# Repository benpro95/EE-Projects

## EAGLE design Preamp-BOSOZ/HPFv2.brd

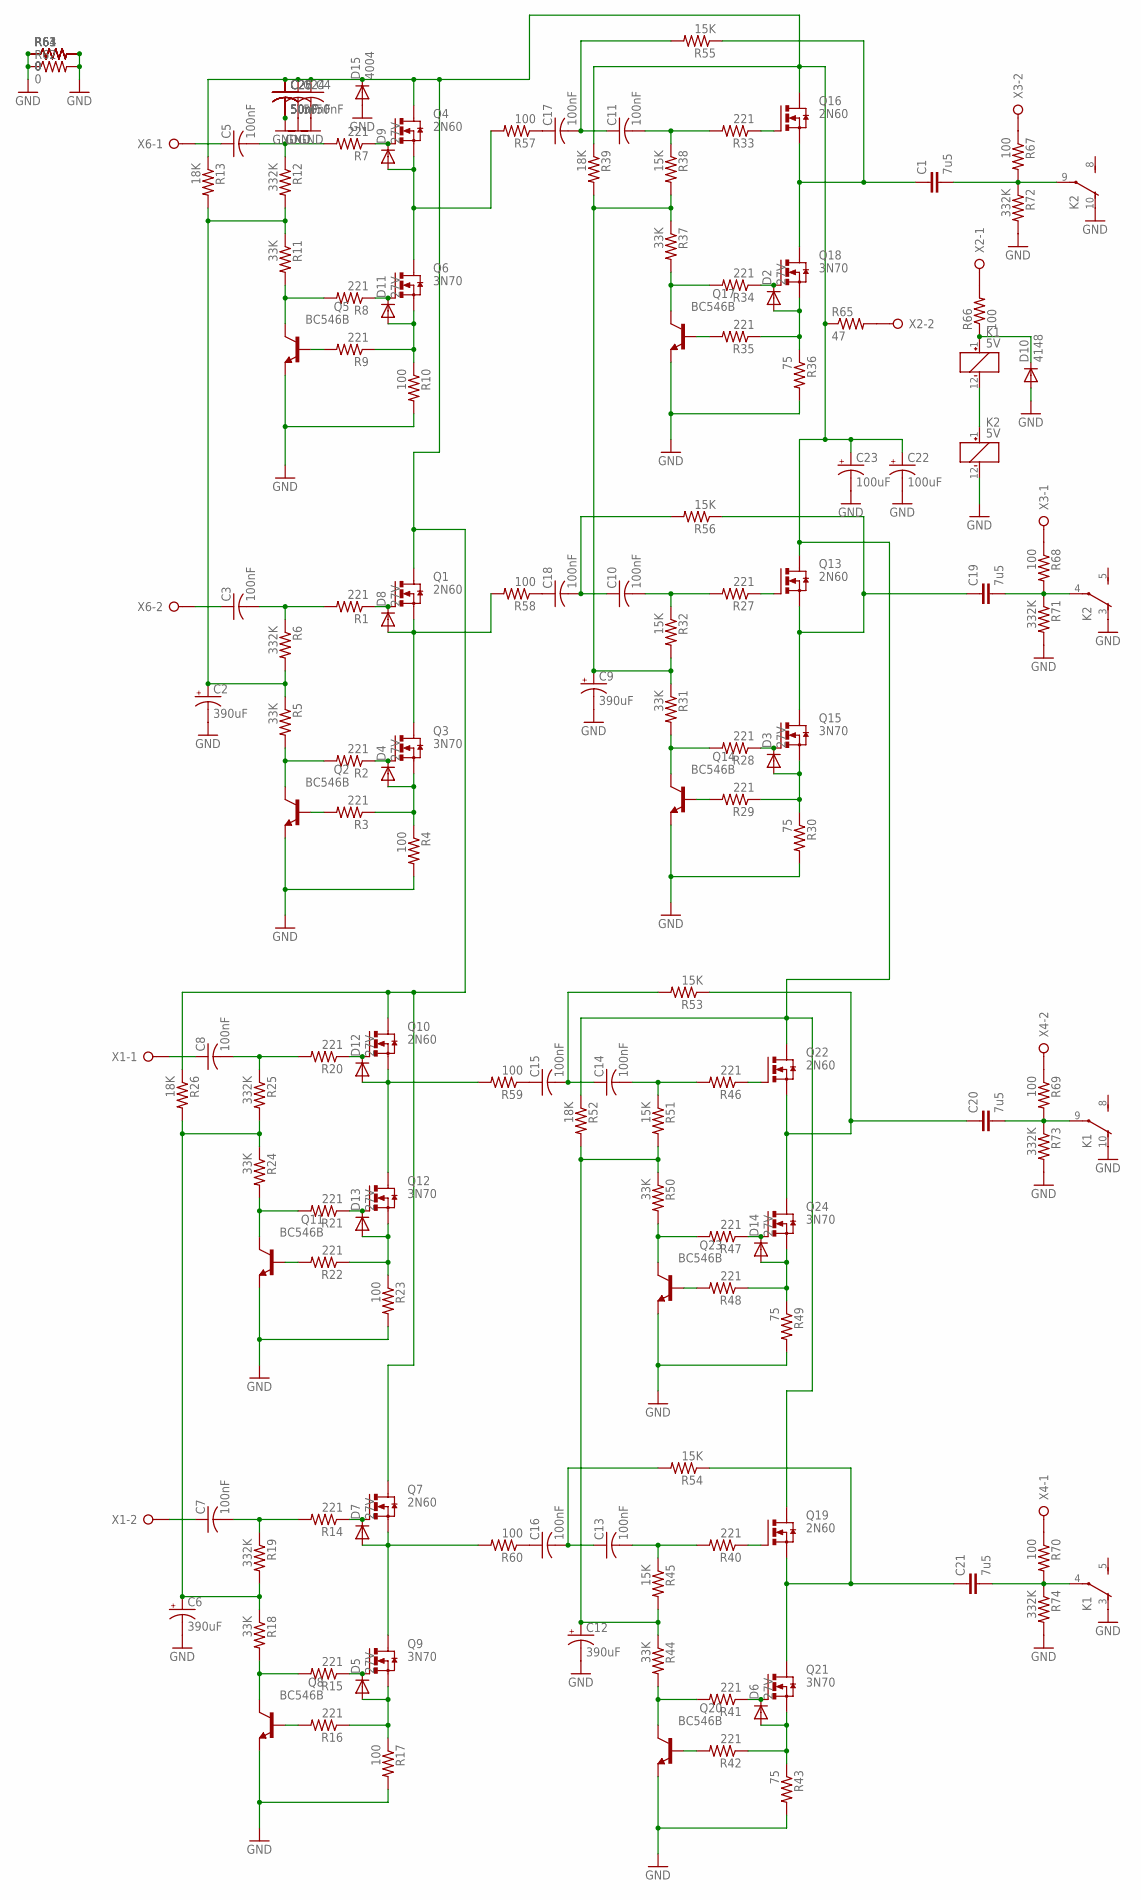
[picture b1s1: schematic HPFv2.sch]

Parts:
C1, C19, C20, C21: 7u5; C37.5B20
C2, C6, C9, C12: 390uF; E5-13
C3, C5, C7, C8, C10, C11, C13, C14, C15, C16, C17, C18: 100nF; C050-075X075
C4, C24, C25, C26, C27: 50nF; C075-042X103
C22, C23: 100uF; E5-13
D2, D3, D4, D5, D6, D7, D8, D9, D11, D12, D13, D14: 27V; DO35-7
D10: 4148; DO35-7
D15: 4004; DO35-10
K1, K2: 5V; TX2
Q1, Q4, Q7, Q10, Q13, Q16, Q19, Q22: 2N60; TO220BH
Q2, Q5, Q8, Q11, Q14, Q17, Q20, Q23: BC546B; TO92-EBC
Q3, Q6, Q9, Q12, Q15, Q18, Q21, Q24: 3N70; TO220BH
R1, R2, R3, R7, R8, R9, R14, R15, R16, R20, R21, R22, R27, R28, R29, R33, R34, R35, R40, R41, R42, R46, R47, R48: 221; 0207/10
R4, R10, R17, R23, R57, R58, R59, R60, R67, R68, R69, R70: 100; 0207/10
R5, R11, R18, R24, R31, R37, R44, R50: 33K; 0207/10
R6, R12, R19, R25, R71, R72, R73, R74: 332K; 0207/10
R13, R26, R39, R52: 18K; 0207/10
R30, R36, R43, R49: 75; 0207/10
R32, R38, R45, R51, R53, R54, R55, R56: 15K; 0207/10
R61, R63, R64: 0; 0207/10
R62: 0; 0204/7
R65: 47; 0617/22
R66: 100; 0309/12
X1, X2, X3, X4, X6: W237-02P; W237-132

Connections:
GND: C2.-, C4.2, C6.-, C9.-, C12.-, C22.-, C23.-, C24.2, C25.2, C26.2, C27.2, D10.A, D15.A, K1.3 (O), K1.10 (O), K2.3 (O), K2.10 (O), K2.12 (-), Q2.E, Q5.E, Q8.E, Q11.E, Q14.E, Q17.E, Q20.E, Q23.E, R4.2, R10.2, R17.2, R23.2, R30.2, R36.2, R43.2, R49.2, R61.1, R61.2, R62.1, R62.2, R63.1, R63.2, R64.1, R64.2, R71.2, R72.2, R73.2, R74.2
unnamed: Q2.B, R3.2
unnamed: D4.A, Q3.S, R3.1, R4.1
unnamed: D4.C, Q3.G, R2.1
unnamed: Q2.C, R2.2, R5.2
unnamed: C3.2, R1.2, R6.1
unnamed: D8.A, Q1.S, Q3.D, R58.2
unnamed: D8.C, Q1.G, R1.1
unnamed: C5.1, X6.1
unnamed: Q5.B, R9.2
unnamed: D11.A, Q6.S, R9.1, R10.1
unnamed: D11.C, Q6.G, R8.1
unnamed: Q5.C, R8.2, R11.2
unnamed: D9.A, Q4.S, Q6.D, R57.2
unnamed: D9.C, Q4.G, R7.1
unnamed: C5.2, R7.2, R12.1
unnamed: C2.+, R5.1, R6.2, R11.1, R12.2, R13.2
unnamed: C4.1, C22.+, C23.+, C24.1, C25.1, C26.1, C27.1, D15.C, Q1.D, Q4.D, Q7.D, Q10.D, Q13.D, Q16.D, Q19.D, Q22.D, R13.1, R26.1, R39.1, R52.1, R65.1
unnamed: C3.1, X6.2
unnamed: Q8.B, R16.2
unnamed: D5.A, Q9.S, R16.1, R17.1
unnamed: D5.C, Q9.G, R15.1
unnamed: Q8.C, R15.2, R18.2
unnamed: D7.A, Q7.S, Q9.D, R60.2
unnamed: D7.C, Q7.G, R14.1
unnamed: C7.2, R14.2, R19.1
unnamed: Q11.B, R22.2
unnamed: D13.A, Q12.S, R22.1, R23.1
unnamed: D13.C, Q12.G, R21.1
unnamed: Q11.C, R21.2, R24.2
unnamed: D12.A, Q10.S, Q12.D, R59.2
unnamed: D12.C, Q10.G, R20.1
unnamed: C8.2, R20.2, R25.1
unnamed: C6.+, R18.1, R19.2, R24.1, R25.2, R26.2
unnamed: C21.2, K1.4, R70.2, R74.1
unnamed: C8.1, X1.1
unnamed: C7.1, X1.2
unnamed: Q14.B, R29.2
unnamed: D3.A, Q15.S, R29.1, R30.1
unnamed: D3.C, Q15.G, R28.1
unnamed: Q14.C, R28.2, R31.2
unnamed: C19.1, Q13.S, Q15.D, R56.1
unnamed: Q13.G, R27.1
unnamed: C10.2, R27.2, R32.1
unnamed: Q17.B, R35.2
unnamed: D2.A, Q18.S, R35.1, R36.1
unnamed: D2.C, Q18.G, R34.1
unnamed: Q17.C, R34.2, R37.2
unnamed: C1.1, Q16.S, Q18.D, R55.1
unnamed: Q16.G, R33.1
unnamed: C11.2, R33.2, R38.1
unnamed: C9.+, R31.1, R32.2, R37.1, R38.2, R39.2
unnamed: C20.2, K1.9, R69.2, R73.1
unnamed: C11.1, C17.2, R55.2
unnamed: C10.1, C18.2, R56.2
unnamed: Q20.B, R42.2
unnamed: D6.A, Q21.S, R42.1, R43.1
unnamed: D6.C, Q21.G, R41.1
unnamed: Q20.C, R41.2, R44.2
unnamed: C21.1, Q19.S, Q21.D, R54.1
unnamed: Q19.G, R40.1
unnamed: C13.2, R40.2, R45.1
unnamed: Q23.B, R48.2
unnamed: D14.A, Q24.S, R48.1, R49.1
unnamed: D14.C, Q24.G, R47.1
unnamed: Q23.C, R47.2, R50.2
unnamed: C20.1, Q22.S, Q24.D, R53.1
unnamed: Q22.G, R46.1
unnamed: C14.2, R46.2, R51.1
unnamed: C12.+, R44.1, R45.2, R50.1, R51.2, R52.2
unnamed: C19.2, K2.4, R68.2, R71.1
unnamed: C14.1, C15.2, R53.2
unnamed: C13.1, C16.2, R54.2
unnamed: C17.1, R57.1
unnamed: C18.1, R58.1
unnamed: C15.1, R59.1
unnamed: C16.1, R60.1
unnamed: C1.2, K2.9, R67.2, R72.1
unnamed: R65.2, X2.2
unnamed: D10.C, K1.1 (+), R66.1
unnamed: R66.2, X2.1
unnamed: R68.1, X3.1
unnamed: R67.1, X3.2
unnamed: R69.1, X4.2
unnamed: R70.1, X4.1
unnamed: K1.12 (-), K2.1 (+)

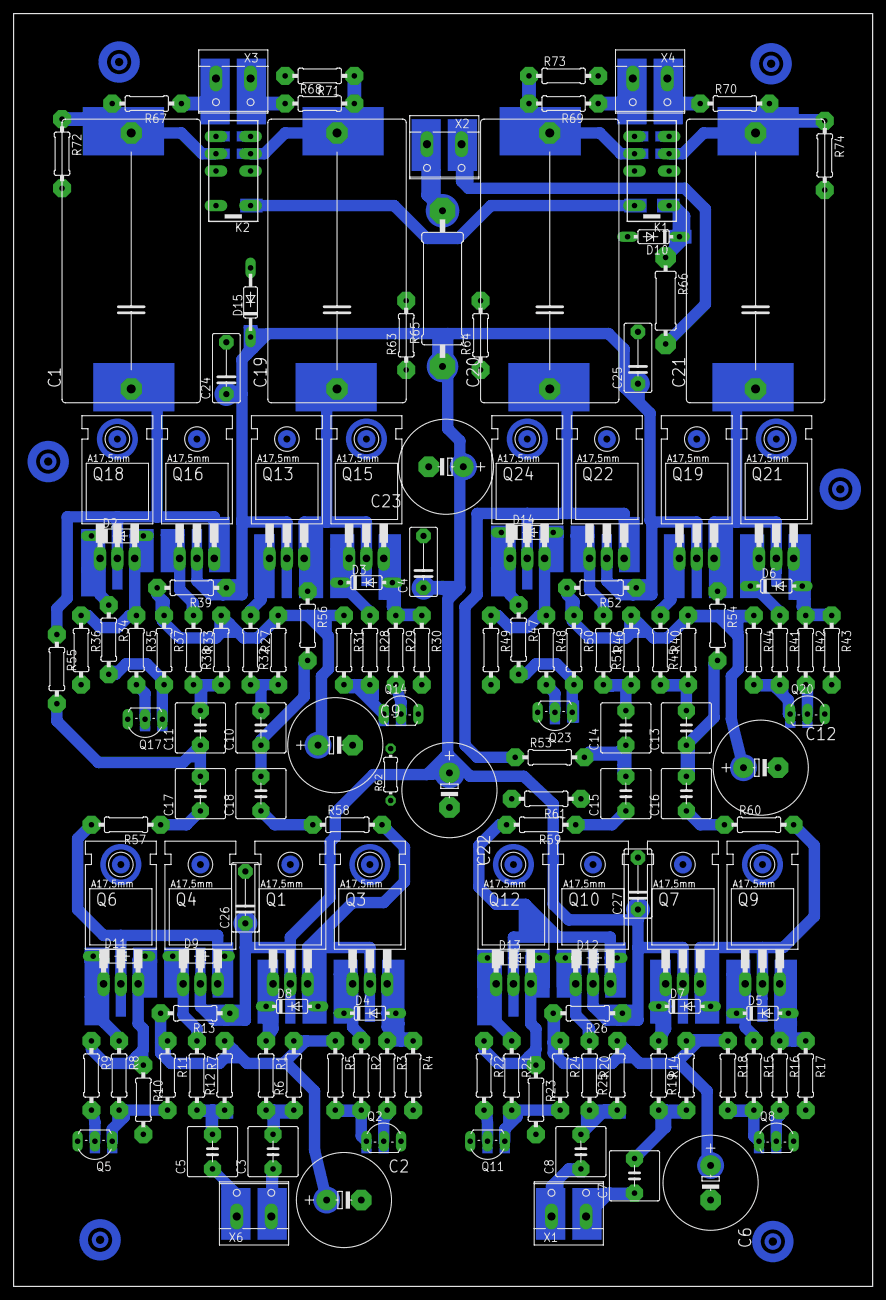
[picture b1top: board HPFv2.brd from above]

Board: 2 copper layers, 126.2 x 186.9 mm, 146 parts (0 on the bottom side), 86 nets.

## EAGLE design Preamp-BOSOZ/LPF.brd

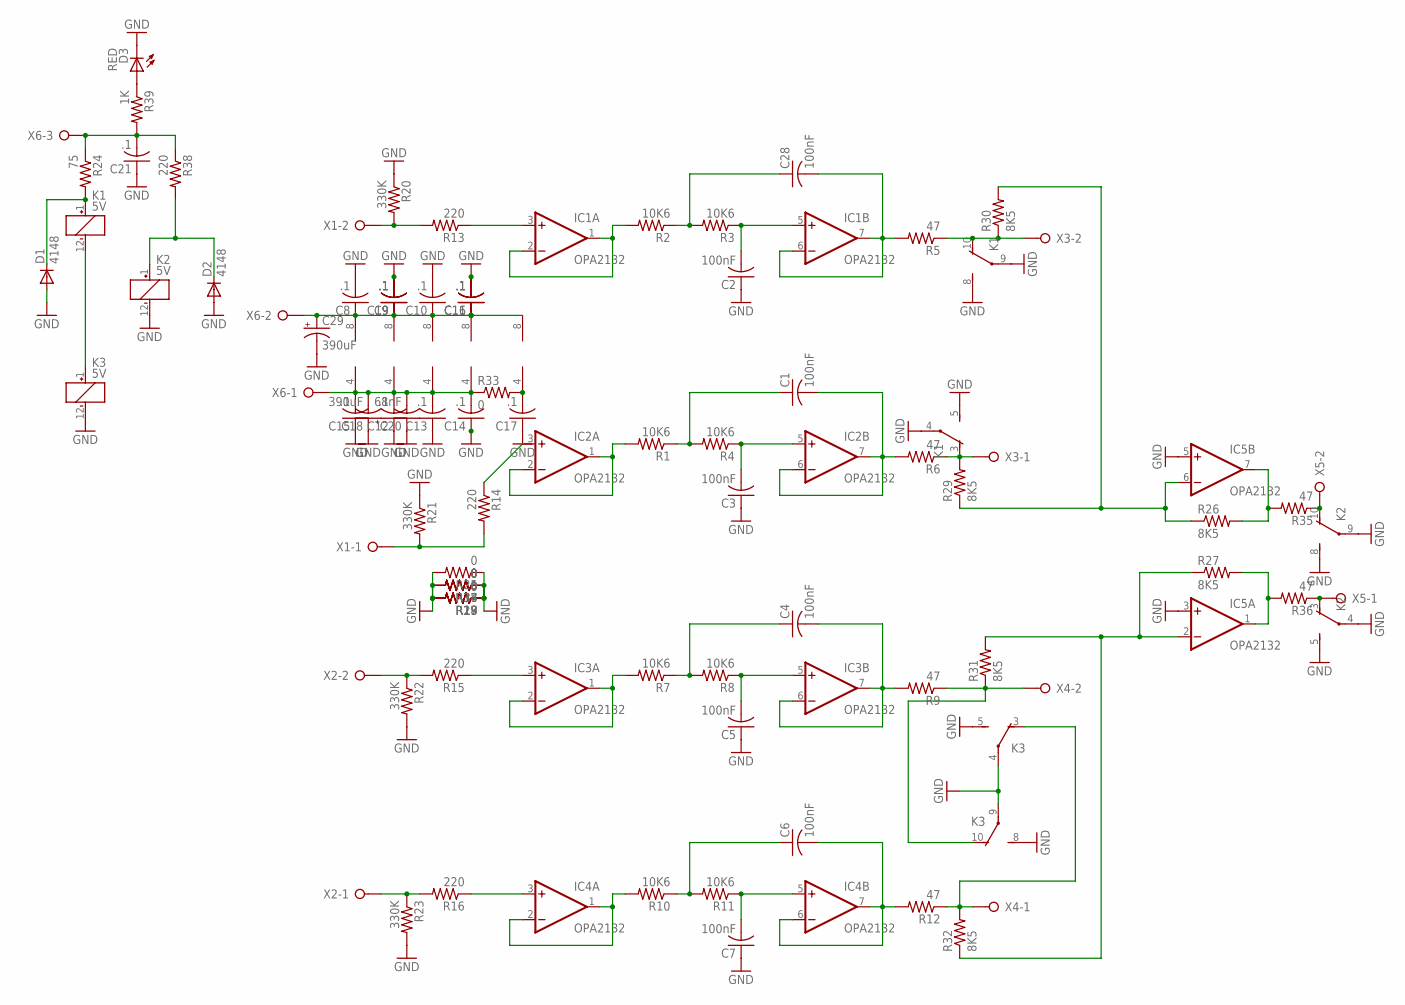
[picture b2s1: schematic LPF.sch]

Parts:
C1, C2, C3, C4, C5, C6, C7, C28: 100nF; C050-075X075
C8, C9, C10, C11, C12, C13, C14, C15, C16, C17, C19, C21: .1; C4532
C18, C29: 390uF; E5-13
C20: 68nF; C075-042X103
D1, D2: 4148; DO35-7
D3: RED; SFH482
IC1, IC2, IC3, IC4, IC5: OPA2132; DIL08
K1, K2, K3: 5V; TX2; MPN TX2-12V
R1, R2, R3, R4, R7, R8, R10, R11: 10K6; 0207/10
R5, R6, R9: 47; 0207/12
R12, R35, R36: 47; 0207/10
R13, R14, R15, R16: 220; 0207/10
R17, R18, R19, R25, R28, R34: 0; 0204/7
R20, R21, R22, R23: 330K; R1210
R24: 75; 0207/10
R26, R27, R29, R30, R31, R32: 8K5; R1210
R33: 0; 0207/12
R37: 0; 0207/10
R38: 220; 0309/12
R39: 1K; 0207/10
X1, X2, X3, X4, X5: W237-02P; W237-132
X6: W237-3E

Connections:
GND: C2.1, C3.1, C5.1, C7.1, C8.2, C9.2, C10.2, C11.2, C12.1, C13.1, C14.1, C15.1, C16.2, C17.1, C18.+, C19.2, C20.1, C21.1, C29.-, D1.A, D2.A, D3.K (C), IC5.3 (+IN), IC5.5 (+IN), K1.4, K1.5 (S), K1.8 (S), K1.9, K2.4, K2.5 (S), K2.8 (S), K2.9, K2.12 (-), K3.4, K3.5 (S), K3.8 (S), K3.9, K3.12 (-), R17.1, R17.2, R18.1, R18.2, R19.1, R19.2, R20.1, R21.1, R22.2, R23.2, R25.1, R25.2, R28.1, R28.2, R34.1, R34.2, R37.1, R37.2
unnamed: IC1.1 (OUT), IC1.2 (-IN), R2.2
unnamed: C28.2, IC1.6 (-IN), IC1.7 (OUT), R5.2
unnamed: C2.2, IC1.5 (+IN), R3.1
unnamed: C28.1, R2.1, R3.2
unnamed: IC1.3 (+IN), R13.1
unnamed: R14.2, R21.2, X1.1
unnamed: R13.2, R20.2, X1.2
unnamed: IC2.1 (OUT), IC2.2 (-IN), R1.2
unnamed: IC2.3 (+IN), R14.1
unnamed: C1.2, IC2.6 (-IN), IC2.7 (OUT), R6.2
unnamed: C3.2, IC2.5 (+IN), R4.1
unnamed: C1.1, R1.1, R4.2
unnamed: C12.2, C13.2, C14.2, C15.2, C18.-, C20.2, IC1.4 (V-), IC2.4 (V-), IC3.4 (V-), IC4.4 (V-), R33.1, X6.1
unnamed: C8.1, C9.1, C10.1, C11.1, C16.1, C19.1, C29.+, IC1.8 (V+), IC2.8 (V+), IC3.8 (V+), IC4.8 (V+), IC5.8 (V+), X6.2
unnamed: IC3.1 (OUT), IC3.2 (-IN), R7.2
unnamed: IC3.3 (+IN), R15.1
unnamed: C4.2, IC3.6 (-IN), IC3.7 (OUT), R9.2
unnamed: C5.2, IC3.5 (+IN), R8.1
unnamed: C4.1, R7.1, R8.2
unnamed: R15.2, R22.1, X2.2
unnamed: R16.2, R23.1, X2.1
unnamed: IC4.1 (OUT), IC4.2 (-IN), R10.2
unnamed: IC4.3 (+IN), R16.1
unnamed: C6.2, IC4.6 (-IN), IC4.7 (OUT), R12.2
unnamed: C7.2, IC4.5 (+IN), R11.1
unnamed: C6.1, R10.1, R11.2
unnamed: K3.3 (O), R12.1, R32.2, X4.1
unnamed: K3.10 (O), R9.1, R31.1, X4.2
unnamed: K1.12 (-), K3.1 (+)
unnamed: K1.10 (O), R5.1, R30.1, X3.2
unnamed: K1.3 (O), R6.1, R29.2, X3.1
unnamed: C17.2, IC5.4 (V-), R33.2
unnamed: D1.C, K1.1 (+), R24.2
unnamed: IC5.6 (-IN), R26.1, R29.1, R30.2
unnamed: IC5.7 (OUT), R26.2, R35.2
unnamed: IC5.1 (OUT), R27.2, R36.2
unnamed: K2.10 (O), R35.1, X5.2
unnamed: IC5.2 (-IN), R27.1, R31.2, R32.1
unnamed: K2.3 (O), R36.1, X5.1
unnamed: D2.C, K2.1 (+), R38.2
unnamed: C21.2, R24.1, R38.1, R39.2, X6.3
unnamed: D3.A, R39.1

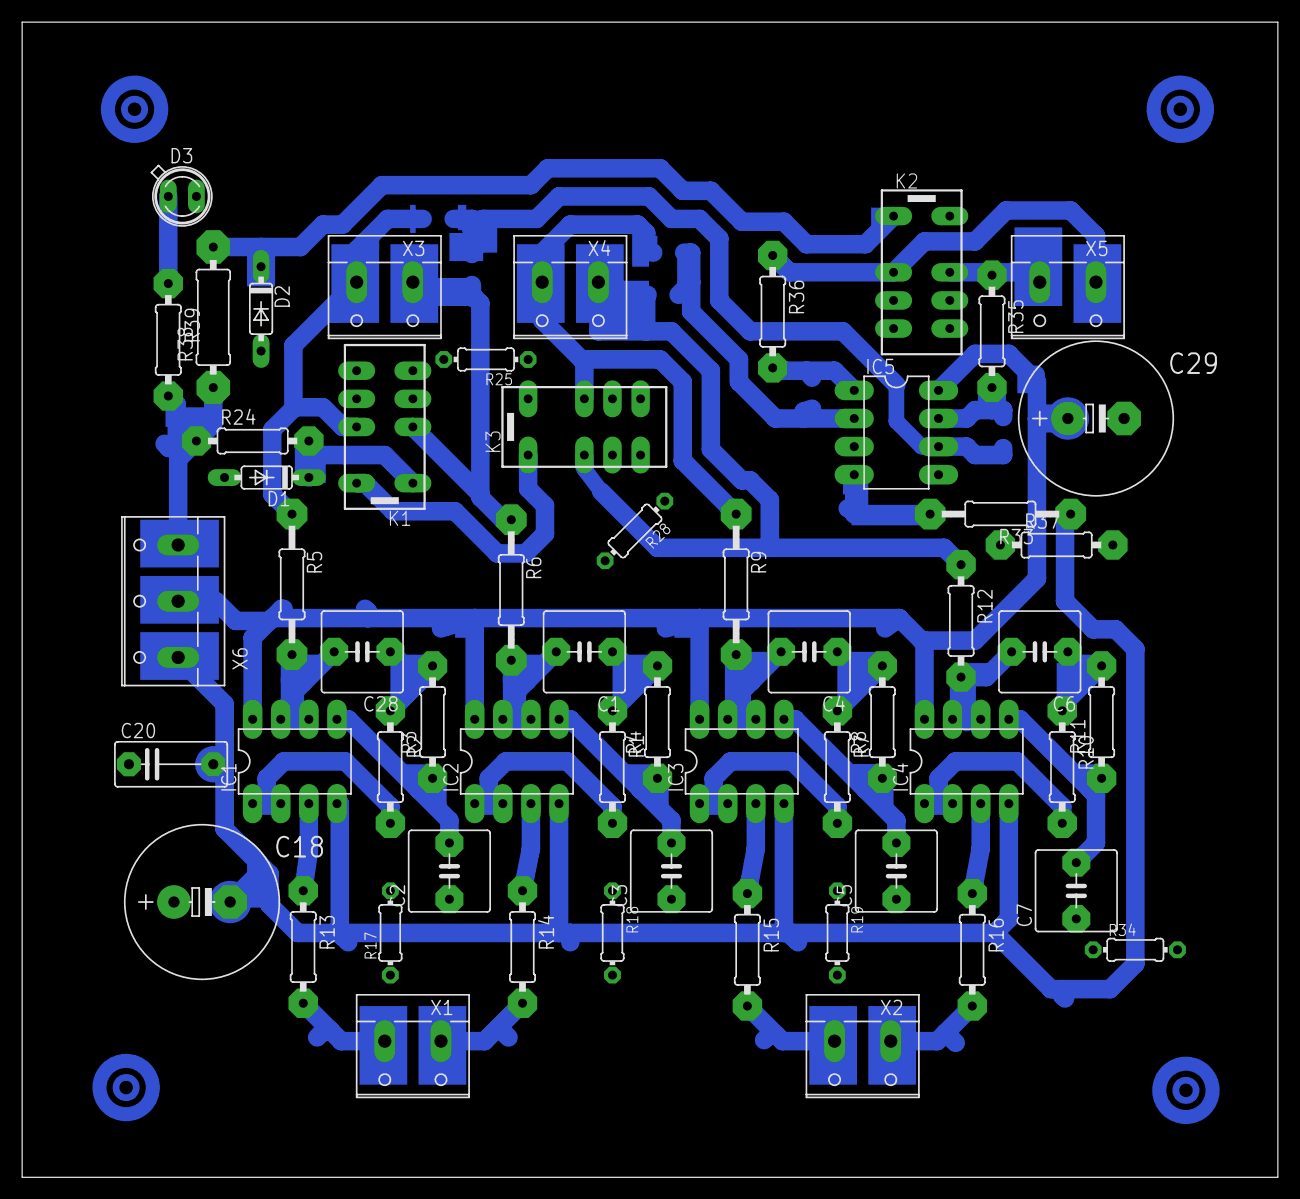
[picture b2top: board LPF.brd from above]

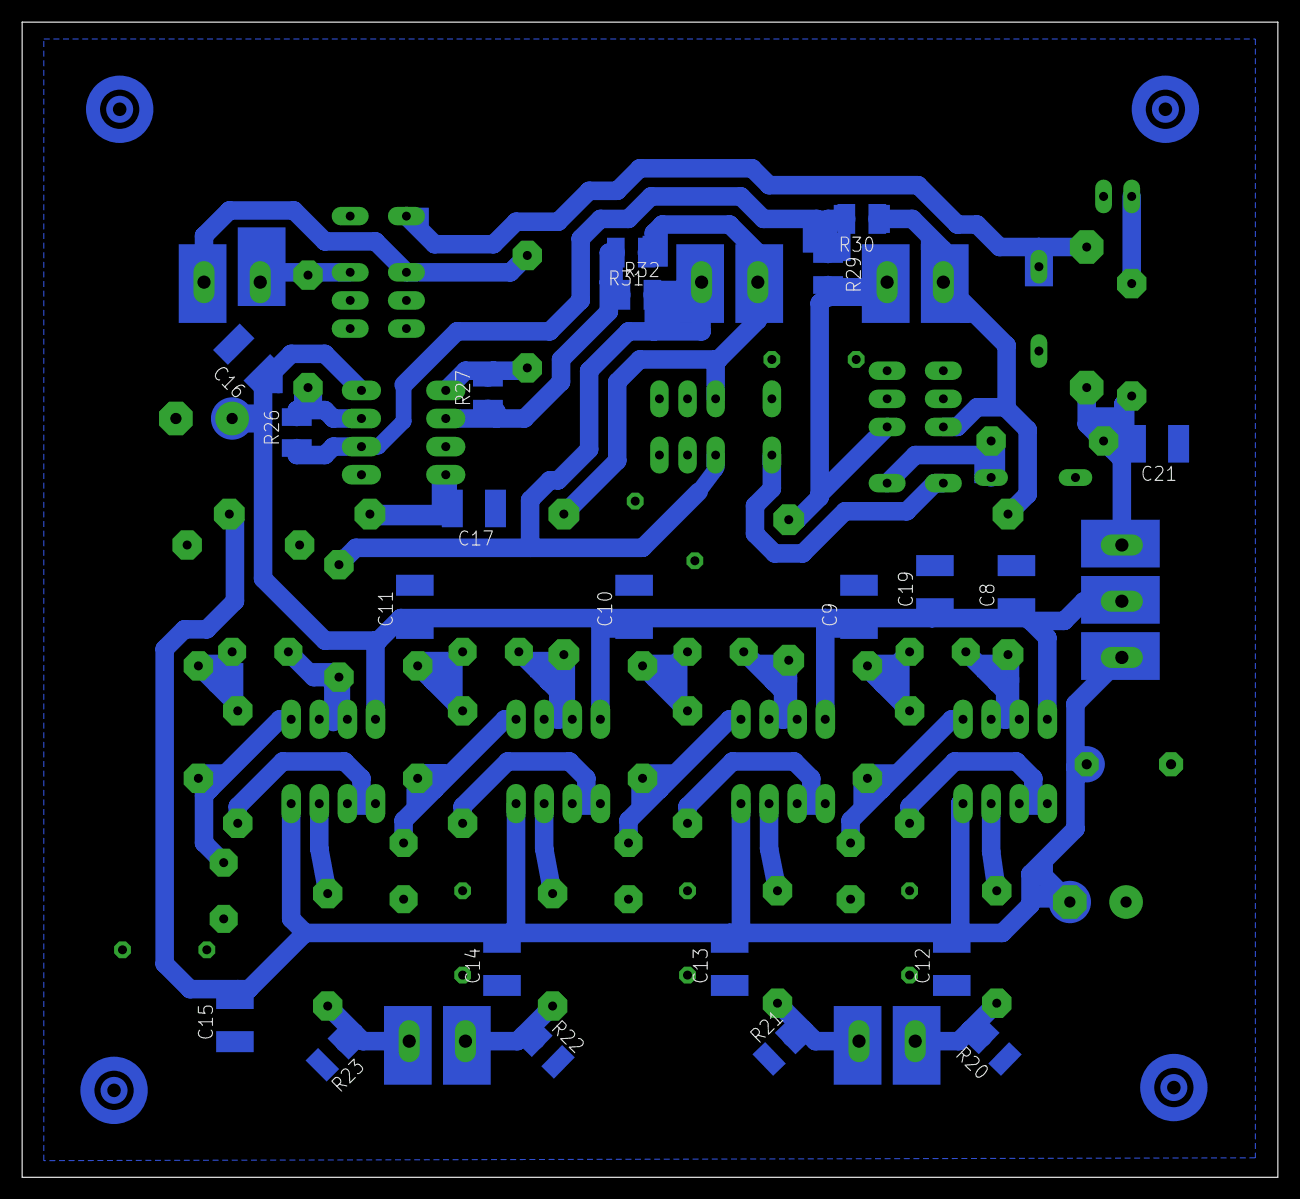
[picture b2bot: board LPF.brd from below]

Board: 2 copper layers, 113.5 x 104.4 mm, 79 parts (22 on the bottom side), 43 nets.

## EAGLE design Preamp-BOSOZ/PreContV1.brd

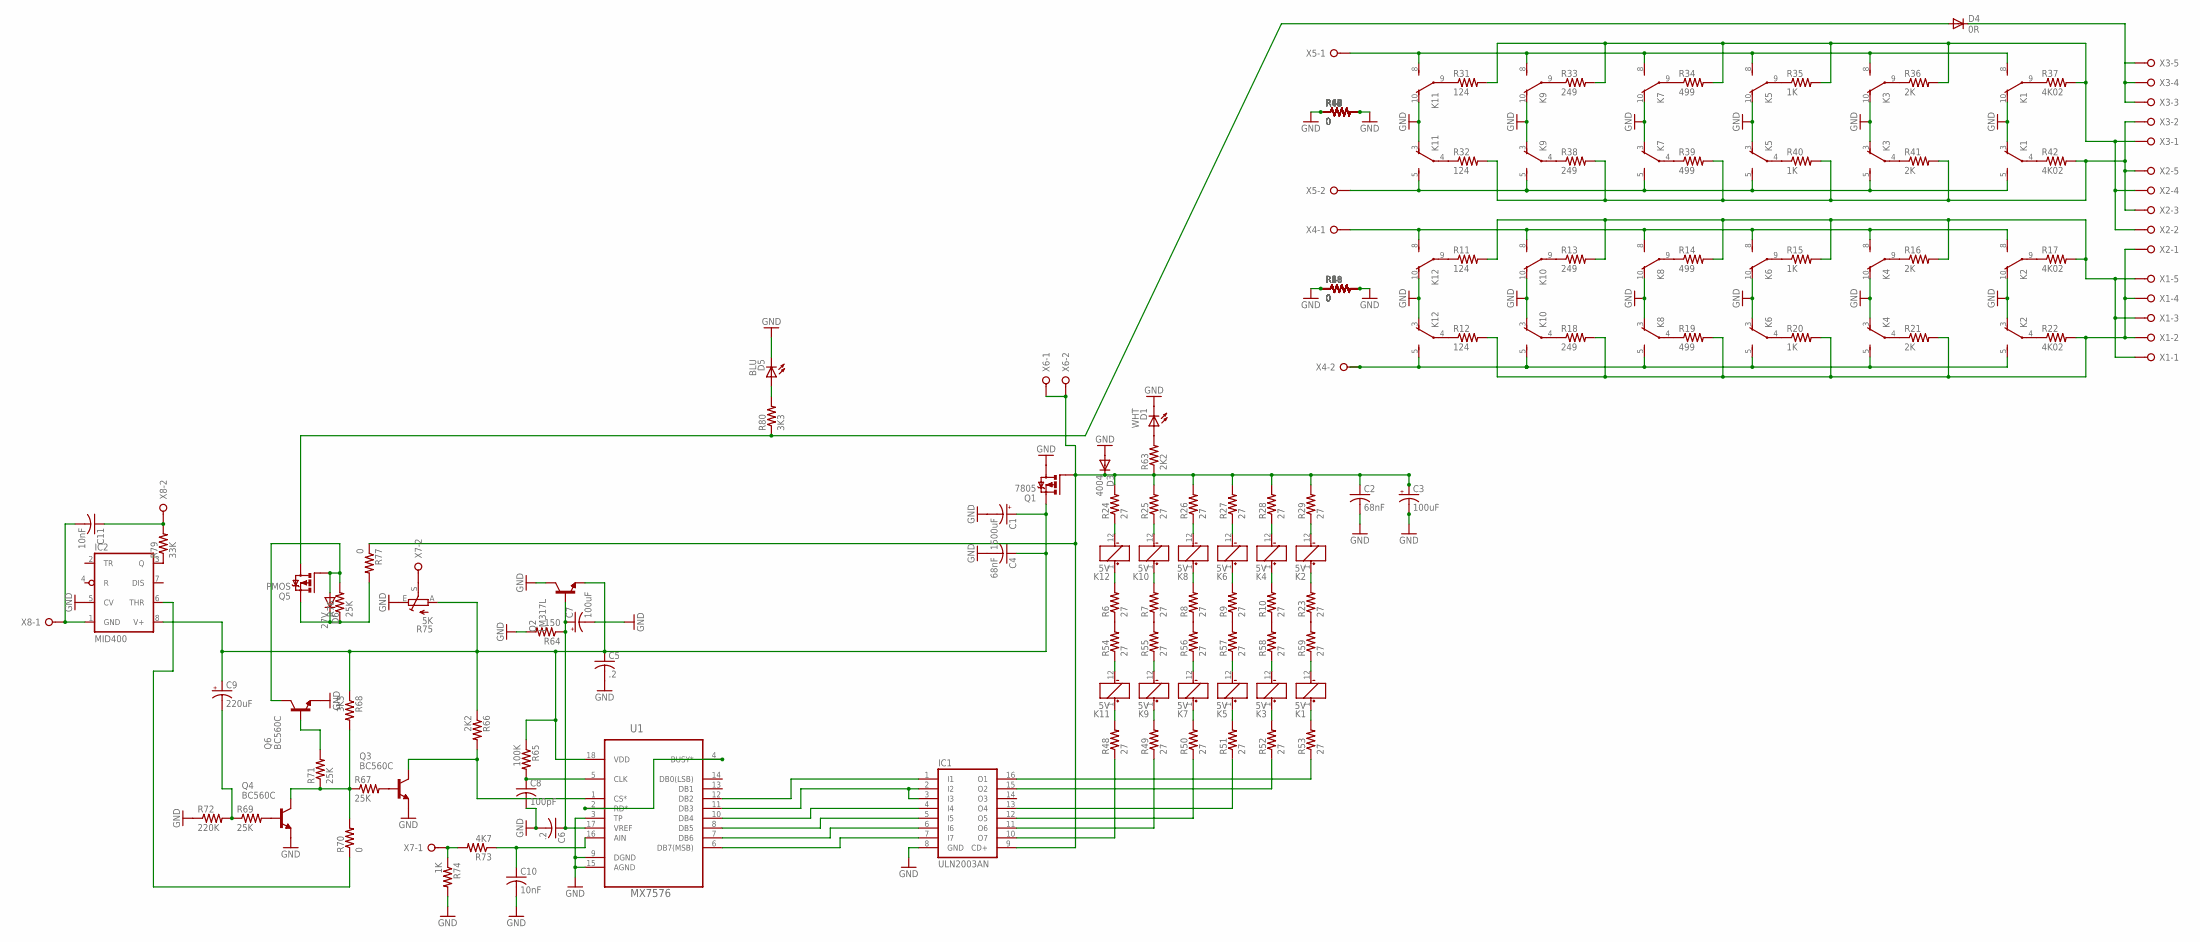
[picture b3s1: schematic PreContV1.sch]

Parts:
C1: 1500uF; E5-10,5
C2, C4: 68nF; C075-042X103
C3, C7: 100uF; E5-10,5
C5, C6: .2; C1210K
C8: 100pF; C050-075X075
C9: 220uF; E5-10,5
C10: 10nF; C050-075X075
C11: 10nF; C075-042X103
D1: WHT; SFH482
D3: 4004; DO35-10
D4: 0R; DO35-10
D5: BLU; SFH482
D6: 27V; DO35-7
IC1: ULN2003AN; DIL16
IC2: MID400; DIL08
K1, K2, K3, K4, K5, K6, K7, K8, K9, K10, K11, K12: 5V; TX2; MPN TX2-12V
Q1: 7805; TO220BH
Q2: LM317L; TO92-EBC
Q3, Q4, Q6: BC560C; TO92-EBC
Q5: PMOS; TO220BH
R1, R2, R3, R4, R5, R30, R43, R44, R45, R46, R47, R60, R61, R62, R70, R77, R78: 0; 0207/10
R6, R7, R8, R9, R10, R23, R24, R25, R26, R27, R28, R29, R48, R49, R50, R51, R52, R53, R59: 27; 0207/10
R11, R12, R31, R32: 124; 0207/10
R13, R18, R33, R38: 249; 0207/10
R14, R19, R34, R39: 499; 0207/10
R15, R20, R35, R40, R74: 1K; 0207/10
R16, R21, R36, R41: 2K; 0207/10
R17, R22, R37, R42: 4K02; 0207/10
R54, R55, R56, R57, R58: 27; 0207/12
R63: 2K2; 0309/12
R64: 150; 0207/10
R65: 100K; 0207/10
R66: 2K2; 0207/10
R67, R69, R71, R76: 25K; 0207/10
R68, R80: 3K3; 0207/10
R72: 220K; 0207/10
R73: 4K7; 0207/10
R75: 5K; RJ9W
R79: 33K; 0309/12
U1: MX7576; DIP254P762X533-18P
X1, X2, X3: W237-05P; W237-5P
X4, X5, X6, X7, X8: W237-02P; W237-132

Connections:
GND: C1.-, C2.2, C3.-, C4.2, C5.2, C6.2, C7.-, C8.2, C10.2, D1.K (C), D3.A, D5.K (C), IC1.8 (GND), IC2.5 (CV), K1.3 (O), K1.10 (O), K2.3 (O), K2.10 (O), K3.3 (O), K3.10 (O), K4.3 (O), K4.10 (O), K5.3 (O), K5.10 (O), K6.3 (O), K6.10 (O), K7.3 (O), K7.10 (O), K8.3 (O), K8.10 (O), K9.3 (O), K9.10 (O), K10.3 (O), K10.10 (O), K11.3 (O), K11.10 (O), K12.3 (O), K12.10 (O), Q1.D, Q2.C, Q3.E, Q4.E, Q6.E, R1.1, R1.2, R2.1, R2.2, R3.1, R3.2, R4.1, R4.2, R5.1, R5.2, R30.1, R30.2, R43.1, R43.2, R44.1, R44.2, R45.1, R45.2, R46.1, R46.2, R47.1, R47.2, R60.1, R60.2, R61.1, R61.2, R62.1, R62.2, R64.2, R72.1, R74.2, R75.E, R78.1, R78.2, U1.3 (TP), U1.9 (DGND), U1.15 (AGND)
unnamed: D4.A, Q5.D, R80.1
unnamed: R32.2, R38.2, R39.2, R40.2, R41.2, R42.2, X2.3, X2.5, X3.2
unnamed: R31.2, R33.2, R34.2, R35.2, R36.2, R37.2, X2.2, X2.4, X3.1
unnamed: K1.8 (S), K3.8 (S), K5.8 (S), K7.8 (S), K9.8 (S), K11.8 (S), X5.1
unnamed: K1.5 (S), K3.5 (S), K5.5 (S), K7.5 (S), K9.5 (S), K11.5 (S), X5.2
unnamed: K11.9, R31.1
unnamed: K11.4, R32.1
unnamed: K2.8 (S), K4.8 (S), K6.8 (S), K8.8 (S), K10.8 (S), K12.8 (S), X4.1
unnamed: K2.5 (S), K4.5 (S), K6.5 (S), K8.5 (S), K10.5 (S), K12.5 (S), X4.2
unnamed: R12.2, R18.2, R19.2, R20.2, R21.2, R22.2, X1.2, X1.4, X2.1
unnamed: K12.1 (+), R6.2
unnamed: K10.1 (+), R7.2
unnamed: K8.1 (+), R8.2
unnamed: K6.1 (+), R9.2
unnamed: R11.2, R13.2, R14.2, R15.2, R16.2, R17.2, X1.1, X1.3, X1.5
unnamed: K4.1 (+), R10.2
unnamed: K2.1 (+), R23.2
unnamed: K12.12 (-), R24.1
unnamed: K10.12 (-), R25.1
unnamed: K12.9, R11.1
unnamed: K12.4, R12.1
unnamed: K10.9, R13.1
unnamed: K8.9, R14.1
unnamed: K6.9, R15.1
unnamed: K2.9, R17.1
unnamed: K4.9, R16.1
unnamed: K10.4, R18.1
unnamed: K8.4, R19.1
unnamed: K6.4, R20.1
unnamed: K4.4, R21.1
unnamed: K2.4, R22.1
unnamed: K8.12 (-), R26.1
unnamed: K6.12 (-), R27.1
unnamed: K4.12 (-), R28.1
unnamed: K2.12 (-), R29.1
unnamed: C2.1, C3.+, D3.C, IC1.9 (CD+), Q1.G, R24.2, R25.2, R26.2, R27.2, R28.2, R29.2, R63.1, R77.1, X6.1, X6.2
unnamed: K9.9, R33.1
unnamed: K7.9, R34.1
unnamed: K5.9, R35.1
unnamed: K1.9, R37.1
unnamed: K3.9, R36.1
unnamed: K9.4, R38.1
unnamed: K7.4, R39.1
unnamed: K5.4, R40.1
unnamed: K3.4, R41.1
unnamed: K1.4, R42.1
unnamed: K11.1 (+), R48.2
unnamed: K9.1 (+), R49.2
unnamed: K7.1 (+), R50.2
unnamed: K5.1 (+), R51.2
unnamed: K3.1 (+), R52.2
unnamed: K1.1 (+), R53.2
unnamed: K11.12 (-), R54.1
unnamed: K9.12 (-), R55.1
unnamed: K7.12 (-), R56.1
unnamed: K5.12 (-), R57.1
unnamed: K3.12 (-), R58.1
unnamed: K1.12 (-), R59.1
unnamed: R6.1, R54.2
unnamed: IC1.10 (O7), R48.1
unnamed: IC1.11 (O6), R49.1
unnamed: R7.1, R55.2
unnamed: R8.1, R56.2
unnamed: R9.1, R57.2
unnamed: R10.1, R58.2
unnamed: R23.1, R59.2
unnamed: IC1.12 (O5), R50.1
unnamed: IC1.13 (O4), R51.1
unnamed: IC1.15 (O2), R52.1
unnamed: IC1.16 (O1), R53.1
unnamed: IC1.7 (I7), U1.6 (DB7(MSB))
unnamed: IC1.6 (I6), U1.7 (DB6)
unnamed: IC1.5 (I5), U1.8 (DB5)
unnamed: IC1.4 (I4), U1.10 (DB4)
unnamed: IC1.2 (I2), IC1.3 (I3), U1.11 (DB3)
unnamed: IC1.1 (I1), U1.12 (DB2)
unnamed: U1.2 (RD*), U1.4 (BUSY*)
unnamed: C1.+, C4.1, C5.1, C9.+, IC2.8 (V+), Q1.S, Q2.E, R65.1, R66.1, R68.1, R75.A, U1.18 (VDD)
unnamed: D1.A, R63.2
unnamed: C6.1, C7.+, Q2.B, R64.1, U1.17 (VREF)
unnamed: Q3.C, R66.2, U1.1 (CS*)
unnamed: C8.1, R65.2, U1.5 (CLK)
unnamed: Q6.B, R71.2
unnamed: C10.1, R73.1, U1.16 (AIN)
unnamed: Q3.B, R67.2
unnamed: Q4.C, R67.1, R68.2, R70.2, R71.1
unnamed: Q4.B, R69.2
unnamed: C9.-, R69.1, R72.2
unnamed: R73.2, R74.1, X7.1
unnamed: R75.S, X7.2
unnamed: D6.A, Q5.G, Q6.C, R76.2
unnamed: IC2.6 (THR), R70.1
unnamed: C11.2, IC2.1 (GND), X8.1
unnamed: IC2.3 (Q), R79.1
unnamed: D6.C, Q5.S, R76.1, R77.2
unnamed: D4.C, X3.3, X3.4, X3.5
unnamed: C11.1, R79.2, X8.2
unnamed: D5.A, R80.2

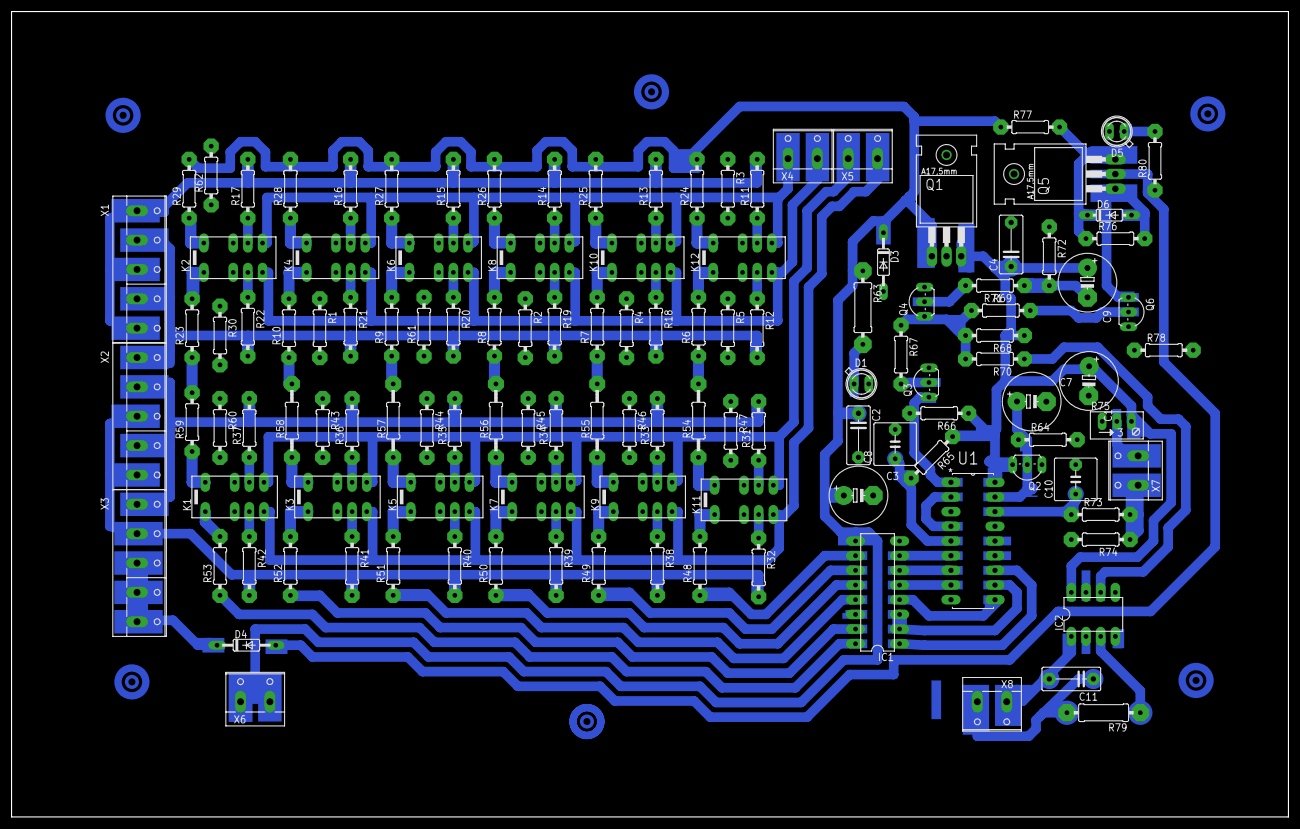
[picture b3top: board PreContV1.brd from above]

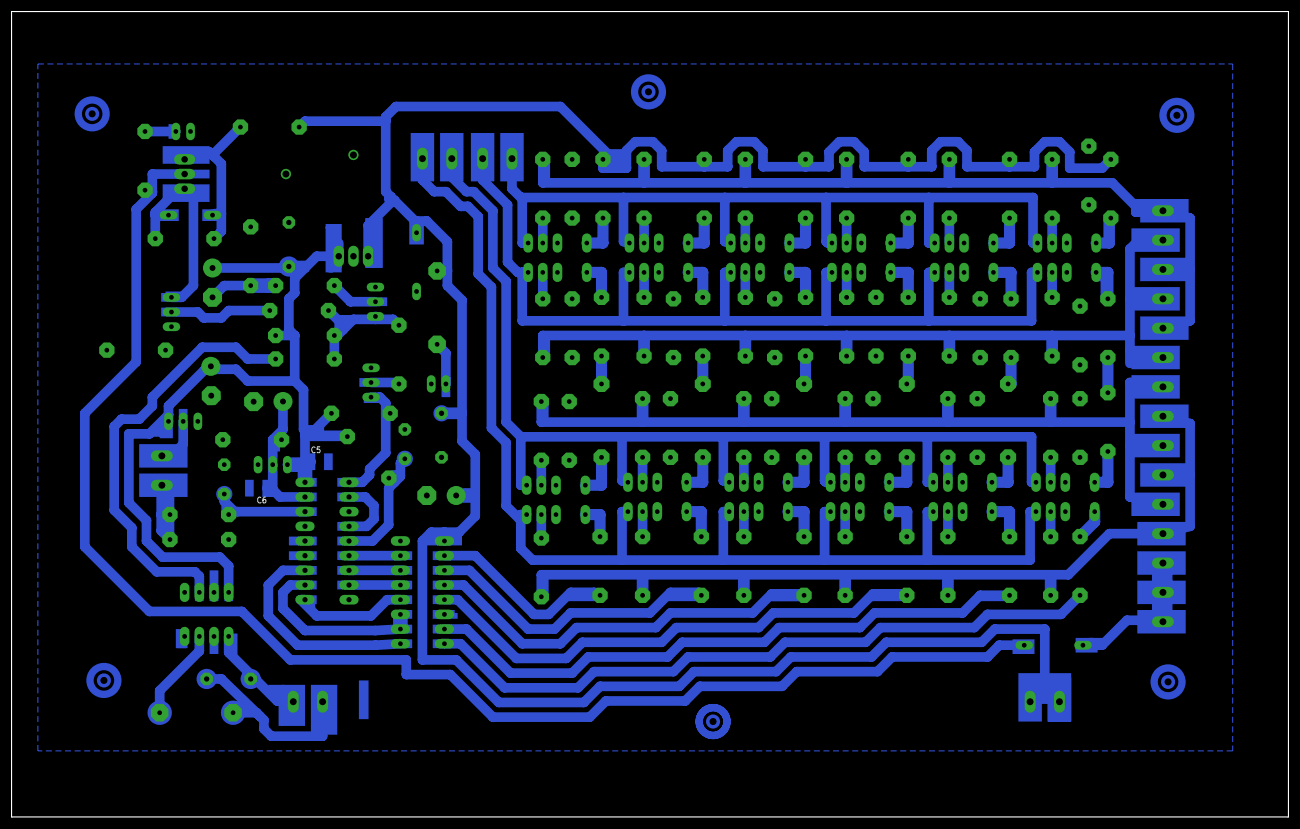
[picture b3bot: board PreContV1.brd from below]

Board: 2 copper layers, 221.0 x 139.4 mm, 125 parts (2 on the bottom side), 99 nets.
